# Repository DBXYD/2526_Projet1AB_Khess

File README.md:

# 🎓 2526_Projet1AB_Khess
> [!Note]
> Projet de 1ère année ENSEA sur une caisse enregistreuse pour la K-Fet.

> [!Important]
> Ce projet reprend en partie le travail de Matis Garbez, disponible sur [2425_Maker_CashRegister](https://github.com/Volcanite/2425_Maker_CashRegister/).

## 📋 Sommaire
- [Cahier des charges](#cahier-des-charges)
	- [Caisse enregistreuse portable avec écran tactile](#caisse-enregistreuse-portable-avec-%C3%A9cran-tactile)
	- [Contraintes](#contraintes)
- [Hardware](#hardware)
- [Modèle 3D de la caisse](#mod%C3%A8le-3d-de-la-caisse)
- [Partie Logicielle (Software)](#partie-logicielle-software)
	- [Accès au Code Source et Déploiement](#acc%C3%A8s-au-code-source-et-d%C3%A9ploiement)
	- [Architecture de la Base de Données](#architecture-de-la-base-de-donn%C3%A9es)
- [Technologies utilisées](#technologies-utilis%C3%A9es)
- [Avancée du projet](#avanc%C3%A9e-du-projet)
	- [Journal de bord](#journal-de-bord)
	- [Ce qui a été réalisé](#ce-qui-a-%C3%A9t%C3%A9-r%C3%A9alis%C3%A9)
	- [Ce qui n'a pas (encore) été réalisé](#ce-qui-na-pas-encore-ete-r%C3%A9alis%C3%A9)
	- [Problèmes rencontrés et solutions trouvées](#probl%C3%A8mes-rencontr%C3%A9s-et-solutions-trouv%C3%A9es)
	- [Améliorations possibles](#am%C3%A9liorations-possibles)
- [Membres du projet](#membres-du-projet)
- [Licence](#licence)

## 📝 Cahier des charges 

### 📱 Caisse enregistreuse portable avec écran tactile 
* Interface utilisateur intuitive
* Gestion des produits et des prix
* Paiement avec carte étudiante

### ⚠️ Contraintes 
* Portabilité (batterie) : terminal de paiement
* Fiabilité des transactions
* Sécurité des données

## 🔧 Hardware 
Voir [Hardware/README.md](Hardware/README.md).

## 🖨️ Modèle 3D de la caisse 
La caisse automatique est consituée de 3 éléments :
- la caisse entière avec le socle
- le module de paiement
- le support pour la tablette
  
La modélisation 3D de ces différentes pièces à été réaliser avec le logiciel Onshape, voici les liens correspondant : 
* [Caisse entière avec socle](3D/Caisse%20entière%20avec%20socle.stl) 
* [Module paiement final](3D/Module%20payement%20final.stl)
* [Support tablette final](3D/Support%20tablette%20final.stl)

## 💻 Partie Logicielle (Software) 
Cette section regroupe l'ensemble du code source de l'application web de la caisse connectée, développée avec le framework **Django** (Python).

### 🔗 Accès au Code Source et Déploiement 

> **Note sur le dépôt :** Suite à des difficultés techniques lors de la synchronisation et de l'envoi du code sur le dépôt partagé de l'équipe, la version la plus récente et totalement à jour de l'application a été temporairement hébergée sur mon espace personnel.

* **Code source à jour :** Vous pouvez consulter et récupérer l'intégralité du projet en [cliquant directement sur ce lien vers mon dépôt personnel](https://github.com/zhang-estelle/DatabaseCashRegister).
* **Guide d'installation :** Pour faire fonctionner le code facilement sur votre machine, j'ai rédigé un guide pas-à-pas. Ce tutoriel recense également l'ensemble des blocages et des problèmes techniques que j'ai rencontrés durant le développement ainsi que leurs solutions. [Consulter le tutoriel de configuration Django](Docs/TutoDjango.md).

### 🗄️ Architecture de la Base de Données 

Le système s'appuie sur une base de données relationnelle structurée pour gérer les profils des étudiants, leurs soldes (cotisants ou non), le catalogue de la K-FET et l'historique des ventes.

* **Modèle Conceptuel :** Pour comprendre l'organisation de nos tables, vous pouvez [accéder au schéma graphique dbdiagram](Docs/dbdiagram.pdf).

## ⚙️ Technologies utilisées 
- Python
- Django
- Raspberry Pi
- KiCad
- Onshape
- Impression 3D

## ✅ Avancée du projet 

### 📓 Journal de bord 
Voir [Journal_de_bord.md](Docs/Journal_de_bord.md).

### ✅ Ce qui a été réalisé 
* Prise en main du projet
* Création des PCB
* Soudure des PCB
* Développement du site internet/ interface vendeur avec gestion des stocks, des commandes
* Modification 3D de la caisse en changeant les dimensions du socle soutenant la tablette
* Modélisation 3D du module de paiement avec plusieurs variantes afin de correspondre à la taille du PCB contenu à l'intérieur
* Développement du code du module de payement
* Modification 3D de la caisse en changeant le support tablette se mettant sur le socle
* Test du PCB

### ❌ Ce qui n'a pas (encore) été réalisé 
* Assemblage de l'ensemble

### 🛠️ Problèmes rencontrés et solutions trouvées 
Modélisation 3D:
- La taille du support de tablette était trop petite ( impossibilité de passer les câbles HDMI et USB vers la caisse automatique ). 
On a du imprimer plusieurs fois le support pour trouver la taille adéquate.
- Les trous pour fixer le support de tablette à son support n'étaient pas au bonne endroit après l'impression, on a du percer avec une perceuse les trous pour fixer le support correctement. 
- Problèmes usuels d'impression 3D.

### 💡 Améliorations possibles 
* Revoir le design de la caisse
* Améliorer le site internet

## 👥 Membres du projet 
|  |  |  |  |  |  |  |
| :---: | :---: | :---: | :---: | :---: | :---: | :---: |
| [@Ahhj93](https://github.com/Ahhj93)<br>Bryan-Sowanna Ing | [@NKRIMAT](https://github.com/NKRIMAT)<br>Naïm Krimat | [@Margaux-Lapl](https://github.com/Margaux-Lapl)<br>Margaux Laplante | [@StrangeKobe](https://github.com/StrangeKobe)<br>Rayan Laghouane | [@zhang-estelle](https://github.com/zhang-estelle)<br>Estelle Zhang | [@ClementJ493](https://github.com/ClementJ493)<br>Clément Jouneau | [@rim-05-mma](https://github.com/rim-05-mma)<br>Rim Bouchikhi |

## 📄 Licence 
Ce projet est distribué sous la licence MIT — voir [LICENSE](LICENSE).

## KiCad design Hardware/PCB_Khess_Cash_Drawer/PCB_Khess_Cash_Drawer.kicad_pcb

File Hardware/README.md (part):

# 🔧 Hardware

## 📋 Sommaire
- [Schéma d'architecture](#schema-architecture)
- [PCB_Khess_Cash_Drawer](#pcb_khess_cash_drawer)
    - [Schéma](#sch%C3%A9ma)
    - [Liste des composants du PCB](#liste-des-composants-du-pcb)
    - [Liste des composants autres](#liste-des-composants-autres)
    - [Justification des choix techniques](#justification-des-choix-techniques)
        - [Architecture d’alimentation](#architecture-dalimentation)
        - [Protections électriques](#protections-%C3%A9lectriques)
        - [Commande du tiroir caisse](#commande-du-tiroir-caisse)
    - [Ouverture du tiroir caisse (Raspberry Pi 4)](#ouverture-du-tiroir-caisse-raspberry-pi-4)
    - [PCB](#pcb)
- [PCB_Khess_Module_Payment](#pcb_khess_module_payment)
    - [Schéma](#sch%C3%A9ma-1)
    - [Liste des composants du PCB](#liste-des-composants-du-pcb-1)
    - [Liste des composants autres](#liste-des-composants-autres-1)
    - [Justification des choix techniques](#justification-des-choix-techniques-1)
        - [Raspberry Pi Zero 2W](#raspberry-pi-zero-2w)
        - [Interface RFID](#interface-rfid)
        - [Interface écran](#interface-%C3%A9cran)
        - [Clavier numérique](#clavier-num%C3%A9rique)
    - [PCB](#pcb-1)

## 🔎 Schéma d'architecture 

Voici une représentation Mermaid du schéma :

```mermaid
flowchart LR
    subgraph Caisse_principale[ Caisse principale ]
        A230(230V AC) --> A12(12V DC)
        A12 --> A5(5V DC)
        A5 --> RPi4[Raspberry Pi 4]
        A12 --> CmdT[Commande tiroir]
        CmdT --> Tiroir[Tiroir caisse]
        RPi4 -->|HDMI| Ecran[Ecran]
        RPi4 -->|GPIO| CmdT
        RPi4 -->|WiFi| Serveur[Serveur]
    end

    subgraph Module_paiement[ Module de paiement ]
        Shield[Shield + gestion batterie] --> RPi0[Raspberry Pi Zero 2W]
        RPi0 -->|HDMI| Ecran2[Ecran]
        RPi0 -->|SPI| RFID[Capteur RFID]
        RPi0 --> Clavier[Clavier]
    end

    RPi4 -->|Bluetooth| RPi0
```

## 🧾 PCB_Khess_Cash_Drawer 
### 🗺️ Schéma 
<details>
<summary>Afficher le schéma</summary>

</details>

### 🔩 Liste des composants du PCB 

* Convertisseur 12V à 5V DC
    * 1 Convertisseur R-78B5.0-2.0 ([datasheet](/Datasheets/PCB_Khess_Cash_Drawer/R-78B-2.0.pdf))
    * 1 Condensateur 10uF
    * 1 Condensateur 4,7uF
    * 1 Bobine 10uH

* Conventisseur 230V à 12V DC
    * 1 Porte-fusible
    * 1 Convertisseur PSK-15E-12 ([datasheet](/Datasheets/PCB_Khess_Cash_Drawer/psk-15e.pdf))
    * 1 Condensateur 100uF
    * 1 Condensateur 1uF
    * 1 Diode TVS (824 500 500) ([datasheet](/Datasheets/PCB_Khess_Cash_Drawer/824500500.pdf))
    * 1 Résistance bobinée 6,8 Ohm (remplacée par un fil) ([datasheet](/Datasheets/PCB_Khess_Cash_Drawer/ac_ac-at_ac-ni.pdf))
    * 1 Varistance TVS 10D561K (non mise) ([datasheet](/Datasheets/PCB_Khess_Cash_Drawer/mov10d.pdf))

* Commande du tiroir caisse
    * 1 Diode DST10100S ([datasheet](/Datasheets/PCB_Khess_Cash_Drawer/littelfuse-rectifier-DST10100S-datasheet.pdf))
    * 1 Transistor BUK9637-100E,118 ([datasheet](/Datasheets/PCB_Khess_Cash_Drawer/BUK9637-100E.pdf))
    * 1 Résistance 220 Ohm
    * 1 Résistance 10k Ohm

* Connecteurs
    * 1 Connecteur 01x03
    * 1 Connecteur RJ11, remplacée par 1 Connecteur 01x02
    * 1 Bornier à vis 01x02
    * 1 Écran tactile

### 📦 Liste des composants autres 

* Tiroir caisse avec connecteur standard RJ11, remplacée par des connecteurs simples
* Câble d'alimentation
* Raspberry Pi 4

## ⚙️ Justification des choix techniques 

### 🔌 Architecture d’alimentation 

L’alimentation du système est réalisée en deux étapes afin d’assurer une conversion efficace et stable :

1. Conversion du secteur 230V AC vers 12V DC ;
2. Conversion du 12V DC vers 5V DC.

Le module **PSK-15E-12** a été choisi car il permet :
- une intégration compacte directement sur le PCB ;
- une puissance suffisante pour alimenter le tiroir caisse et les circuits logiques.

Le convertisseur **R-78B5.0-2.0** a été préféré à un régulateur linéaire classique pour son excellent rendement énergétique. Cela permet - d’éviter l’ajout d’un dissipateur thermique ;
- d’assurer une alimentation stable du Raspberry Pi.

Les condensateurs et la bobine de filtrage permettent de réduire les parasites haute fréquence et d’améliorer la stabilité des tensions d’alimentation.

### 🛡️ Protections électriques 

Plusieurs composants de protection ont été ajoutés afin d’améliorer la robustesse du système :

- le porte-fusible protège la carte en cas de court-circuit ;
- la diode TVS protège contre les surtensions transitoires ;
- la varistance devait initialement renforcer la protection contre les pics secteur ;
- les condensateurs participent au filtrage des perturbations électromagnétiques.

Ces protections sont importantes car le système est directement relié au secteur et pilote une charge inductive.

### ⚡ Commande du tiroir caisse 

Le tiroir caisse est commandé via un MOSFET de puissance **BUK9637-100E**. Ce composant a été choisi pour :
- sa faible résistance à l’état passant ;
- sa capacité à commuter des courants importants ;
- sa compatibilité avec les niveaux logiques du Raspberry Pi.

La diode **DST10100S** agit comme diode de roue libre afin d’absorber les surtensions générées lors de la coupure du courant dans l’électroaimant du tiroir caisse.

La résistance de 220 Ω limite le courant de commande du MOSFET tandis que la résistance de 10 kΩ garantit son extinction au démarrage.

### 🚪 Ouverture du tiroir caisse (Raspberry Pi 4) 

L’ouverture du tiroir caisse se fait via le PCB :

1. La **Raspberry Pi 4** envoie un signal de commande sur un **GPIO** ;
2. Le GPIO pilote la grille du **MOSFET** sur le PCB ;
3. Le MOSFET commute l’alimentation **12V** de l’électroaimant du tiroir ;
4. Le tiroir caisse s’ouvre pendant l’impulsion.

Nous n’avions pas de port **RJ11** disponible sur notre montage.  
Nous avons donc remplacé les connecteurs RJ11 par des **pinheaders**.

### 🧩 PCB 
<details>
<summary>Voir PCB (face côté avant)</summary>

</details>

<details>
<summary>Voir PCB (face arrière)</summary>

</details>

---

## 🧾 PCB_Khess_Module_Payment 
### 🗺️ Schéma 
<details>
<summary>Afficher le schéma</summary>

</details>

### 🔩 Liste des composants du PCB 

* Raspberry Pi
    * 1 Connecteur 02x20
    * 1 Diode TVS (824 500 500) ([datasheet](/Datasheets/PCB_Khess_Cash_Drawer/824500500.pdf))
    * 2 Résistances 470 Ohm
    * 2 LED
    * 1 Condensateur 100nF

* RFID
    * 1 Connecteur 01x08
    * 1 Condensateur 1uF

* Écran
    * 1 Condensateur 1uF
    * 1 Connecteur 01x04
    * 2 Résistances 4,7k Ohm

* Clavier numérique
    * 4 Résistances 10k Ohm
    * 4 Résistances 330 Ohm
    * 1 Connecteurs 01x08

### 📦 Liste des composants autres 

* 1 Raspberry Zero 2W
* 1 Écran tactile
* 1 Clavier numérique
* 1 Capteur RFID
* 1 Shield pour gérer une batterie

### ⚙️ Justification des choix techniques 

#### 🖥️ Raspberry Pi Zero 2W 

Le Raspberry Pi Zero 2W a été choisi comme unité centrale du module de paiement pour plusieurs raisons :
- faible consommation énergétique ;
- connectivité Wi-Fi intégrée ;
- puissance suffisante pour gérer l’interface utilisateur et les périphériques.

#### 🛰️ Interface RFID 

Le module RFID permet l’identification sans contact des utilisateurs.

Le connecteur 01x08 qui permet la comminication via le bus SPI, facilite le remplacement ou la maintenance du module RFID. Le condensateur de 1 µF améliore la stabilité de son alimentation et limite les perturbations lors des communications.

#### 🖱️ Interface écran 

L’écran tactile est connecté via une interface dédiée afin de simplifier le montage.

Les résistances de pull-up de 4,7 kΩ servent de résistances de tirage pour les lignes de communication utilisées en I2C.

Le condensateur de 1 µF stabilise l’alimentation de l’écran et réduit les parasites.

#### 🔢 Clavier numérique 

Le clavier numérique permet une interaction simple avec l’utilisateur et sert dans le cas où l'utilisateur ne possède pas sa carte.

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
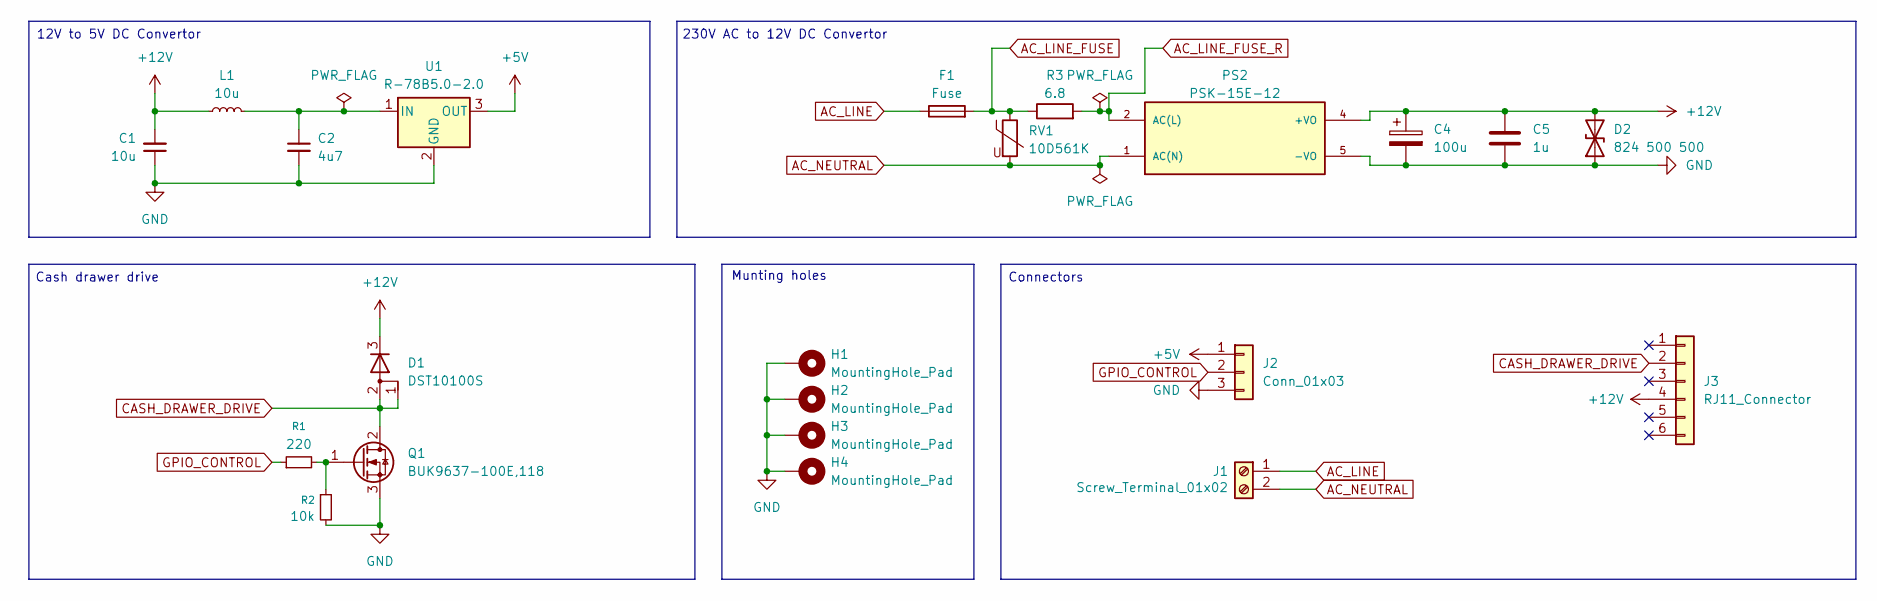
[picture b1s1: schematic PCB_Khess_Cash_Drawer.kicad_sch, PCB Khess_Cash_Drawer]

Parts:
C1: 10u; C_0805_2012Metric
C2: 4u7; C_0805_2012Metric
C4: 100u; CP_Elec_6.3x7.7
C5: 1u; C_0805_2012Metric
D1: DST10100S; TO-277A
D2: 824 500 500; D_SMA
F1: Fuse; Fuseholder_Cylinder-5x20mm_Schurter_0031_8201_Horizontal_Op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
H1, H2, H3, H4: MountingHole_Pad; MountingHole_2.7mm_M2.5_Pad
J1: Screw_Terminal_01x02; TerminalBlock_Phoenix_PT-1,5-2-5.0-H_1x02_P5.00mm_Horizontal
J2: Conn_01x03; PinHeader_1x03_P2.54mm_Vertical
J3: RJ11_Connector; RJ12_Amphenol_54601-x06_Horizontal
L1: 10u; L_0805_2012Metric
PS2: PSK-15E-12; CONV_PSK-15E-12; PARTREV 1.0
Q1: BUK9637-100E,118; TO-263-2
R1: 220; R_0603_1608Metric
R2: 10k; R_0603_1608Metric
R3: 6.8; R_Axial_DIN0414_L11.9mm_D4.5mm_P20.32mm_Horizontal
RV1: 10D561K; VAR_MOV-10D561K
U1: R-78B5.0-2.0; Converter_DCDC_RECOM_R-78B-2.0_THT

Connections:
+5V: J2.1, U1.3 (OUT)
+12V: C1.2, C4.1, C5.1, D1.3 (K), D2.2 (A2), J3.4, L1.1, PS2.4 (+VO)
AC_LINE: F1.1, J1.1
AC_LINE_FUSE: F1.2, R3.1, RV1.1
AC_LINE_FUSE_R: PS2.2 (AC(L)), R3.2
AC_NEUTRAL: J1.2, PS2.1 (AC(N)), RV1.2
CASH_DRAWER_DRIVE: D1.1 (A), D1.2 (A), J3.2, Q1.2 (D)
GND: C1.1, C2.2, C4.2, C5.2, D2.1 (A1), H1.1, H2.1, H3.1, H4.1, J2.3, PS2.5 (-VO), Q1.3 (S), R2.2, U1.2 (GND)
GPIO_CONTROL: J2.2, R1.1
unnamed: Q1.1 (G), R1.2, R2.1
unnamed: C2.1, L1.2, U1.1 (IN)

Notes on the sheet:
Connectors
230V AC to 12V DC Convertor
Munting holes
Cash drawer drive
12V to 5V DC Convertor

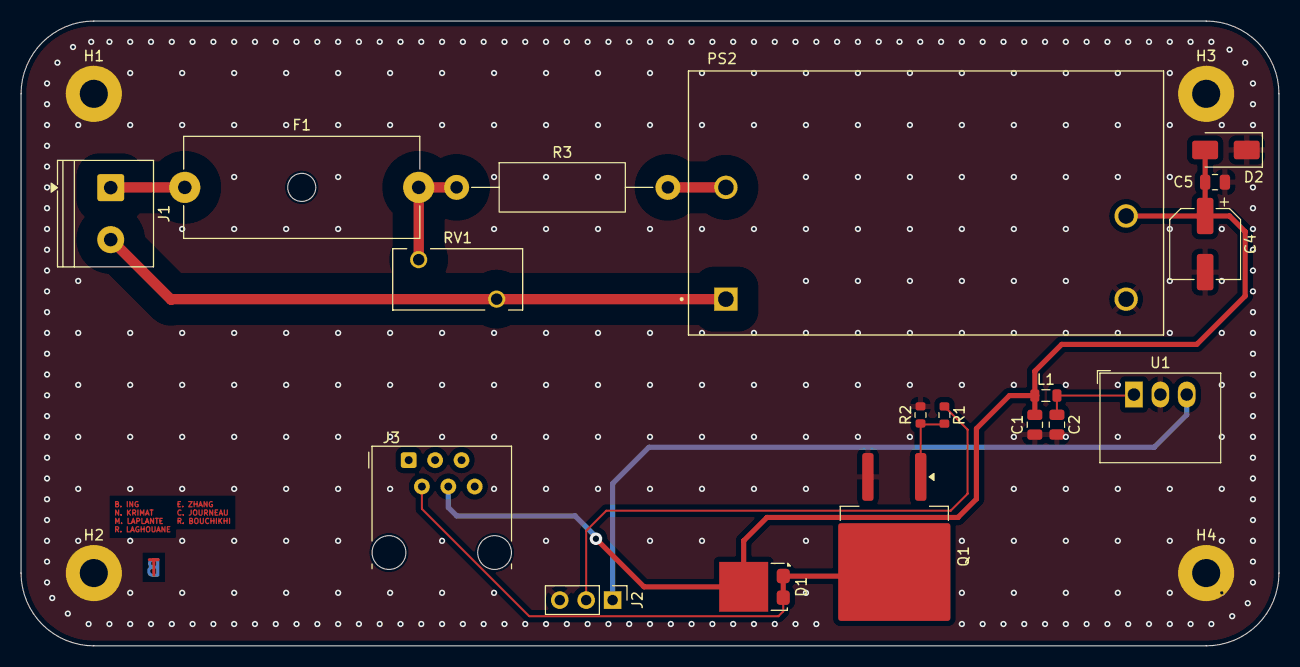
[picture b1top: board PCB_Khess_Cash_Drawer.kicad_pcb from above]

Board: 2 copper layers, 121.0 x 60.1 mm, 22 parts (0 on the bottom side), 11 nets.

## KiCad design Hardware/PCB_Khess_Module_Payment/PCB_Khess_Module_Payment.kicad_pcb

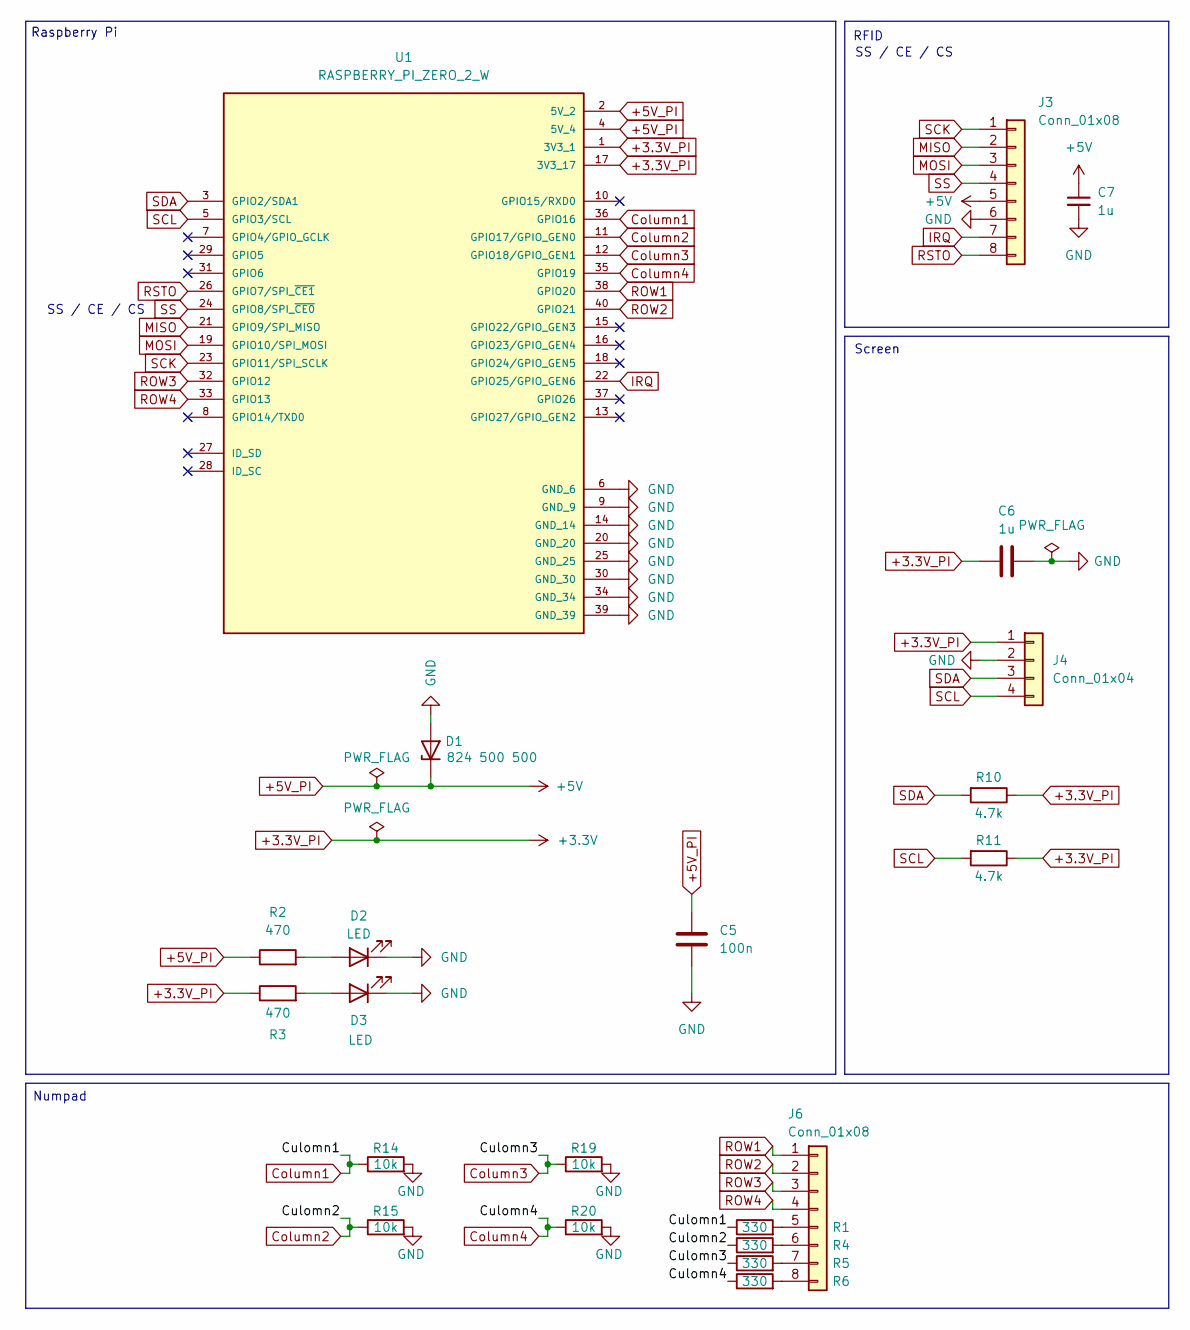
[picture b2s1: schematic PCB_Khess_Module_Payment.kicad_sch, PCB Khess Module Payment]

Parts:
C5: 100n; C_0402_1005Metric
C6, C7: 1u; C_0603_1608Metric
D1: 824 500 500; D_SMA
D2, D3: LED; LED_0603_1608Metric
J3, J6: Conn_01x08; PinHeader_1x08_P2.54mm_Horizontal
J4: Conn_01x04; PinHeader_1x04_P2.54mm_Horizontal
R1, R4, R5, R6: 330; R_0402_1005Metric
R2, R3: 470; R_0805_2012Metric
R10, R11: 4.7k; R_0402_1005Metric
R14, R15, R19, R20: 10k; R_0805_2012Metric
U1: RASPBERRY_PI_ZERO_2_W; MODULE_RASPBERRY_PI_ZERO_2_W; PARTREV April 2024

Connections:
+3.3V_PI: C6.1, J4.1, R3.1, R10.1, R11.1, U1.1 (3V3_1), U1.17 (3V3_17)
+5V_PI: C5.1, C7.1, D1.1 (K), J3.5, R2.1, U1.2 (5V_2), U1.4 (5V_4)
Column1: R1.1, R14.1, U1.36 (GPIO16)
Column2: R4.1, R15.1, U1.11 (GPIO17/GPIO_GEN0)
Column3: R5.1, R19.1, U1.12 (GPIO18/GPIO_GEN1)
Column4: R6.1, R20.1, U1.35 (GPIO19)
GND: C5.2, C6.2, C7.2, D1.2 (A), D2.1 (K), D3.1 (K), J3.6, J4.2, R14.2, R15.2, R19.2, R20.2, U1.6 (GND_6), U1.9 (GND_9), U1.14 (GND_14), U1.20 (GND_20), U1.25 (GND_25), U1.30 (GND_30), U1.34 (GND_34), U1.39 (GND_39)
IRQ: J3.7, U1.22 (GPIO25/GPIO_GEN6)
MISO: J3.2, U1.21 (GPIO9/SPI_MISO)
MOSI: J3.3, U1.19 (GPIO10/SPI_MOSI)
unnamed: D2.2 (A), R2.2
unnamed: D3.2 (A), R3.2
unnamed: J6.5, R1.2
unnamed: J6.6, R4.2
unnamed: J6.7, R5.2
unnamed: J6.8, R6.2
ROW1: J6.1, U1.38 (GPIO20)
ROW2: J6.2, U1.40 (GPIO21)
ROW3: J6.3, U1.32 (GPIO12)
ROW4: J6.4, U1.33 (GPIO13)
RSTO: J3.8, U1.26 (GPIO7/SPI_~CE1)
SCK: J3.1, U1.23 (GPIO11/SPI_SCLK)
SCL: J4.4, R11.2, U1.5 (GPIO3/SCL)
SDA: J4.3, R10.2, U1.3 (GPIO2/SDA1)
SS: J3.4, U1.24 (GPIO8/SPI_~CE0)

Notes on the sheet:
RFID
Raspberry Pi
Numpad
Screen
SS / CE / CS

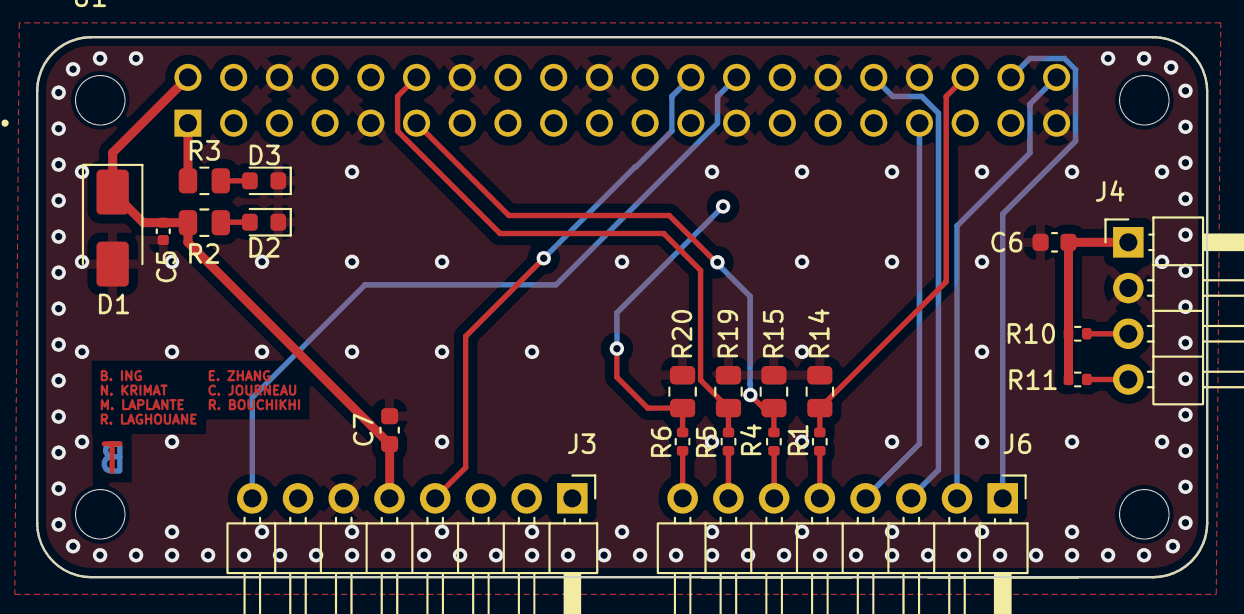
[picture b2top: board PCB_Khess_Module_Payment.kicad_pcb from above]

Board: 4 copper layers, 65.0 x 30.0 mm, 22 parts (0 on the bottom side), 25 nets.

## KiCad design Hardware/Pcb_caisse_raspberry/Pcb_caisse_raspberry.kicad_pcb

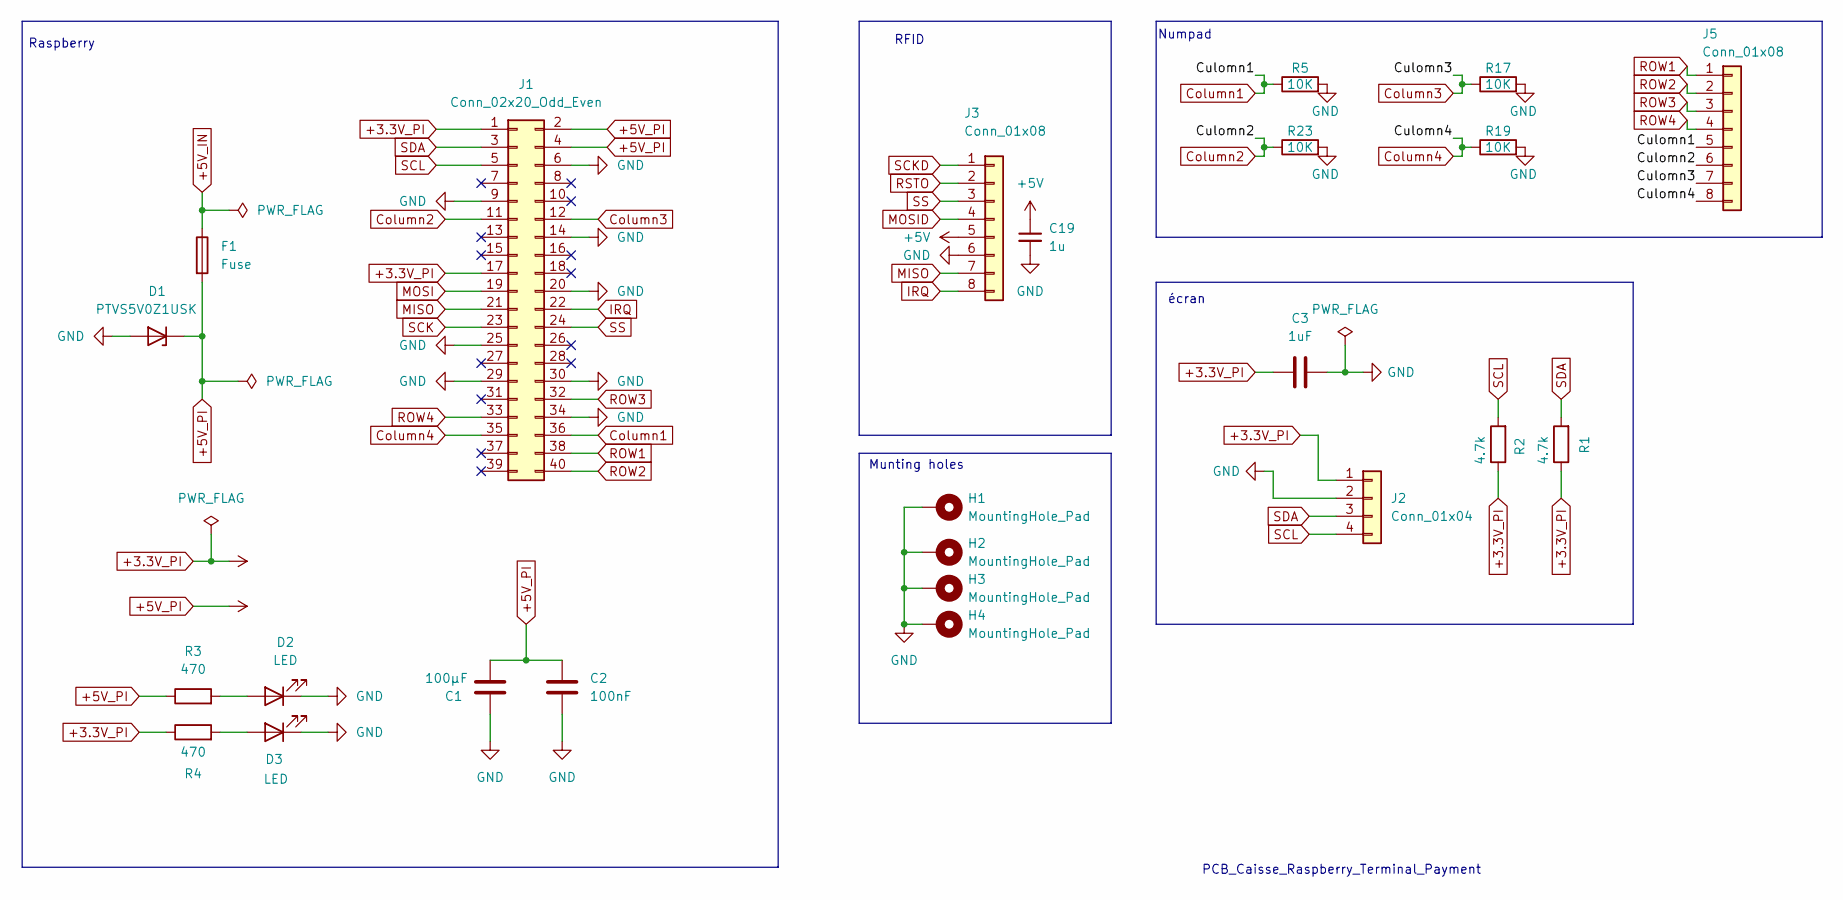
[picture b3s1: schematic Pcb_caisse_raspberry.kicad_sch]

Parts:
C1: 100µF; C_0603_1608Metric_Pad1.08x0.95mm_HandSolder
C2: 100nF; C_0603_1608Metric_Pad1.08x0.95mm_HandSolder
C3: 1uF; C_0603_1608Metric_Pad1.08x0.95mm_HandSolder
C19: 1u; C_0603_1608Metric_Pad1.08x0.95mm_HandSolder
D1: PTVS5V0Z1USK; Nexperia_DSN1608-2_1.6x0.8mm
D2, D3: LED; LED_0603_1608Metric_Pad1.05x0.95mm_HandSolder
F1: Fuse; FuseHolder_Blade_ATO_Littelfuse_FLR_178.6165
H1, H2, H3, H4: MountingHole_Pad; MountingHole_2.7mm_M2.5_Pad
J1: Conn_02x20_Odd_Even; PinHeader_2x20_P1.00mm_Vertical
J2: Conn_01x04; PinHeader_1x04_P2.54mm_Horizontal
J3, J5: Conn_01x08; PinHeader_1x08_P2.54mm_Horizontal
R1, R2: 4.7k; R_0603_1608Metric_Pad0.98x0.95mm_HandSolder
R3, R4: 470; R_0603_1608Metric_Pad0.98x0.95mm_HandSolder
R5, R17, R19, R23: 10K; R_0402_1005Metric

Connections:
+3.3V_PI: C3.1, J1.1, J1.17, J2.1, R1.1, R2.1, R4.1
+5V_IN: F1.1
+5V_PI: C1.2, C2.1, C19.1, D1.1 (K), F1.2, J1.2, J1.4, J3.5, R3.1
Column1: J1.36, J5.5, R5.1
Column2: J1.11, J5.6, R23.1
Column3: J1.12, J5.7, R17.1
Column4: J1.35, J5.8, R19.1
GND: C1.1, C2.2, C3.2, C19.2, D1.2 (A), D2.1 (K), D3.1 (K), H1.1, H2.1, H3.1, H4.1, J1.6, J1.9, J1.14, J1.20, J1.25, J1.29, J1.30, J1.34, J2.2, J3.6, R5.2, R17.2, R19.2, R23.2
IRQ: J1.22, J3.8
MISO: J1.21, J3.7
MOSI: J1.19
MOSID: J3.4
unnamed: D2.2 (A), R3.2
unnamed: D3.2 (A), R4.2
ROW1: J1.38, J5.1
ROW2: J1.40, J5.2
ROW3: J1.32, J5.3
ROW4: J1.33, J5.4
RSTO: J3.2
SCK: J1.23
SCKD: J3.1
SCL: J1.5, J2.4, R2.2
SDA: J1.3, J2.3, R1.2
SS: J1.24, J3.3

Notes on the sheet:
Munting holes
RFID
Raspberry
Numpad
écran
PCB_Caisse_Raspberry_Terminal_Payment

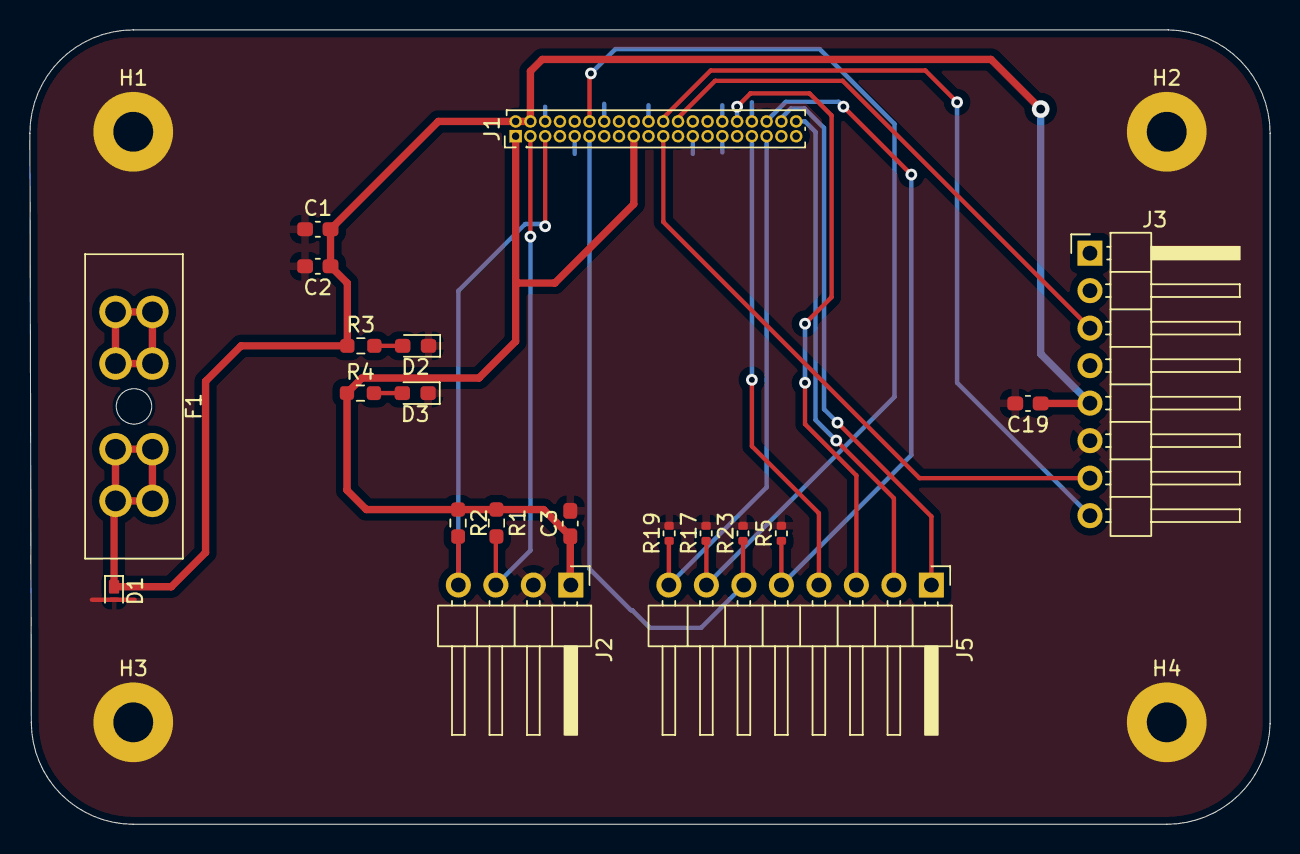
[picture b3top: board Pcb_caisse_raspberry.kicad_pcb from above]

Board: 2 copper layers, 84.0 x 53.8 mm, 24 parts (0 on the bottom side), 18 nets.

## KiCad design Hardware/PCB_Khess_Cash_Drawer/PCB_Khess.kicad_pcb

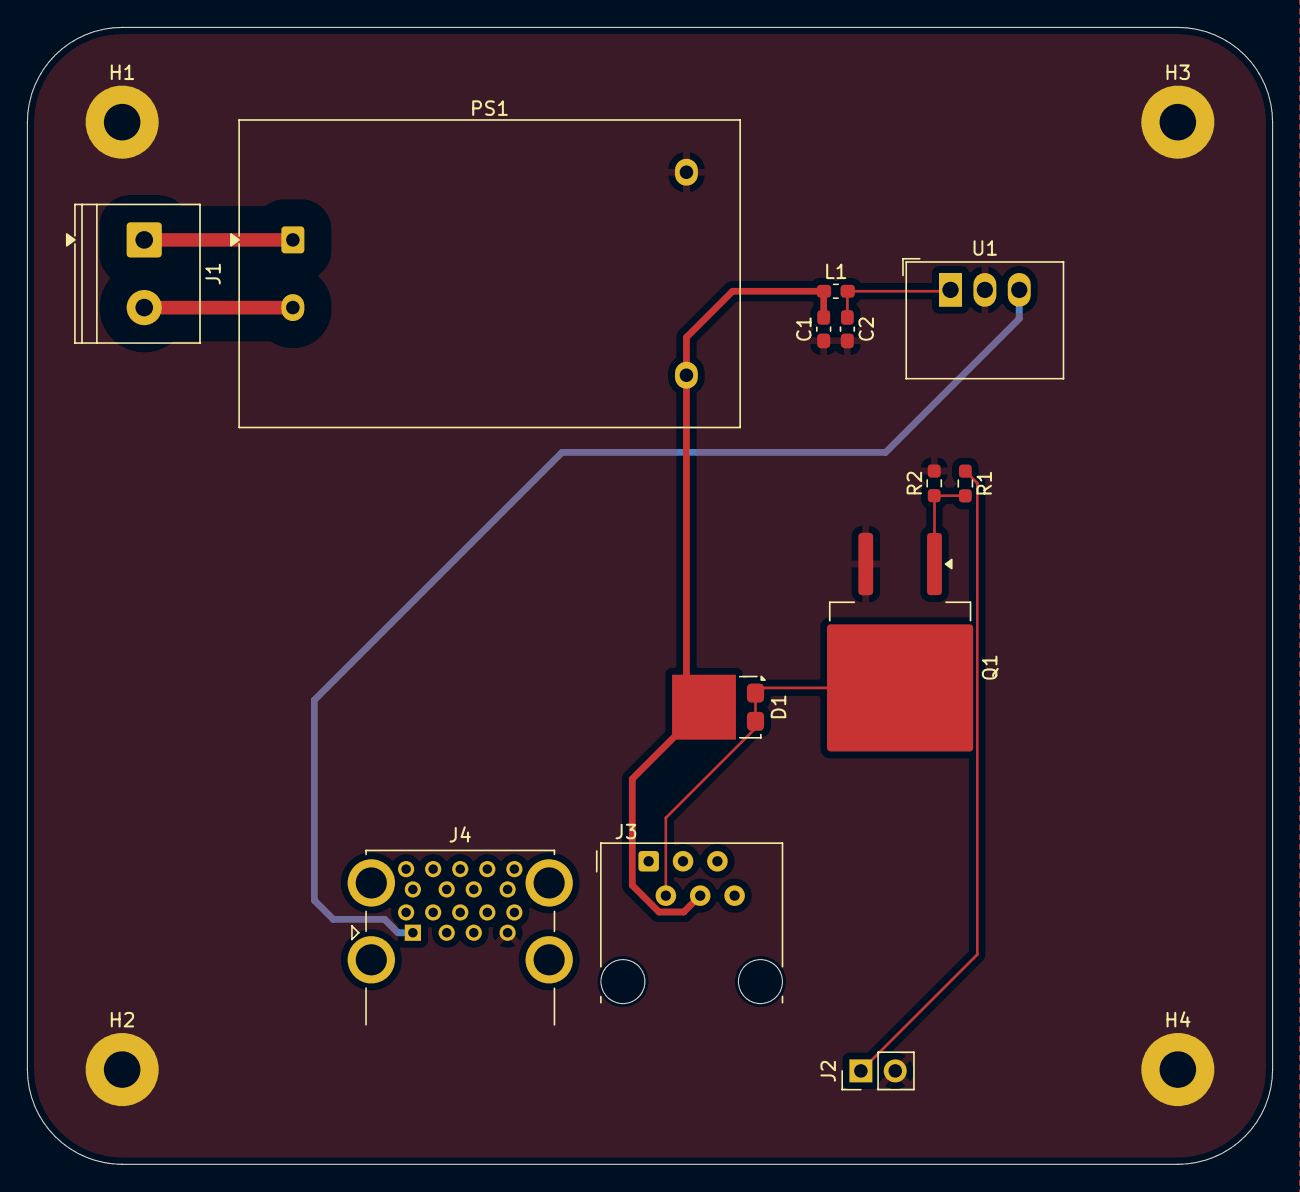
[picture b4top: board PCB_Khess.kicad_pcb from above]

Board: 2 copper layers, 92.0 x 84.0 mm, 17 parts (0 on the bottom side), 9 nets.

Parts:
C1: 10u; C_0603_1608Metric_Pad1.08x0.95mm_HandSolder
C2: 4.7u; C_0603_1608Metric_Pad1.08x0.95mm_HandSolder
D1: DST10100S; TO-277A
H1, H2, H3, H4: MountingHole_Pad; MountingHole_2.7mm_M2.5_Pad
J1: Screw_Terminal_01x02; TerminalBlock_Phoenix_PT-1,5-2-5.0-H_1x02_P5.00mm_Horizontal
J2: Conn_01x02; PinHeader_1x02_P2.54mm_Vertical
J3: RJ11_Connector; RJ12_Amphenol_54601-x06_Horizontal
J4: USB3_A; USB3_A_Molex_48406-0001_Horizontal_Stacked
L1: 10u; L_0603_1608Metric_Pad1.05x0.95mm_HandSolder
PS1: HLK-PM12; Converter_ACDC_Hi-Link_HLK-PMxx
Q1: BUK9637-100E,118; TO-263-2
R1: 220; R_0603_1608Metric_Pad0.98x0.95mm_HandSolder
R2: 10k; R_0603_1608Metric_Pad0.98x0.95mm_HandSolder
U1: R-78B5.0-2.0; Converter_DCDC_RECOM_R-78B-2.0_THT

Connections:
+5V: J4.1 (VBUS), U1.3 (OUT)
AC_LINE: J1.1, PS1.1 (AC/L)
AC_NEUTRAL: J1.2, PS1.2 (AC/N)
CASH_DRAWER_DRIVE: D1.1 (A), D1.2 (A), J3.2, Q1.2 (D)
CASH_DRAWER_VCC: C1.2, D1.3 (K), J3.4, L1.1, PS1.4 (+Vout)
GND: C1.1, C2.2, H1.1, H2.1, H3.1, H4.1, J2.2, J4.4 (GND), PS1.3 (-Vout), Q1.3 (S), R2.2, U1.2 (GND)
GPIO_CONTROL: J2.1, R1.1
unnamed: Q1.1 (G), R1.2, R2.1
unnamed: C2.1, L1.2, U1.1 (IN)

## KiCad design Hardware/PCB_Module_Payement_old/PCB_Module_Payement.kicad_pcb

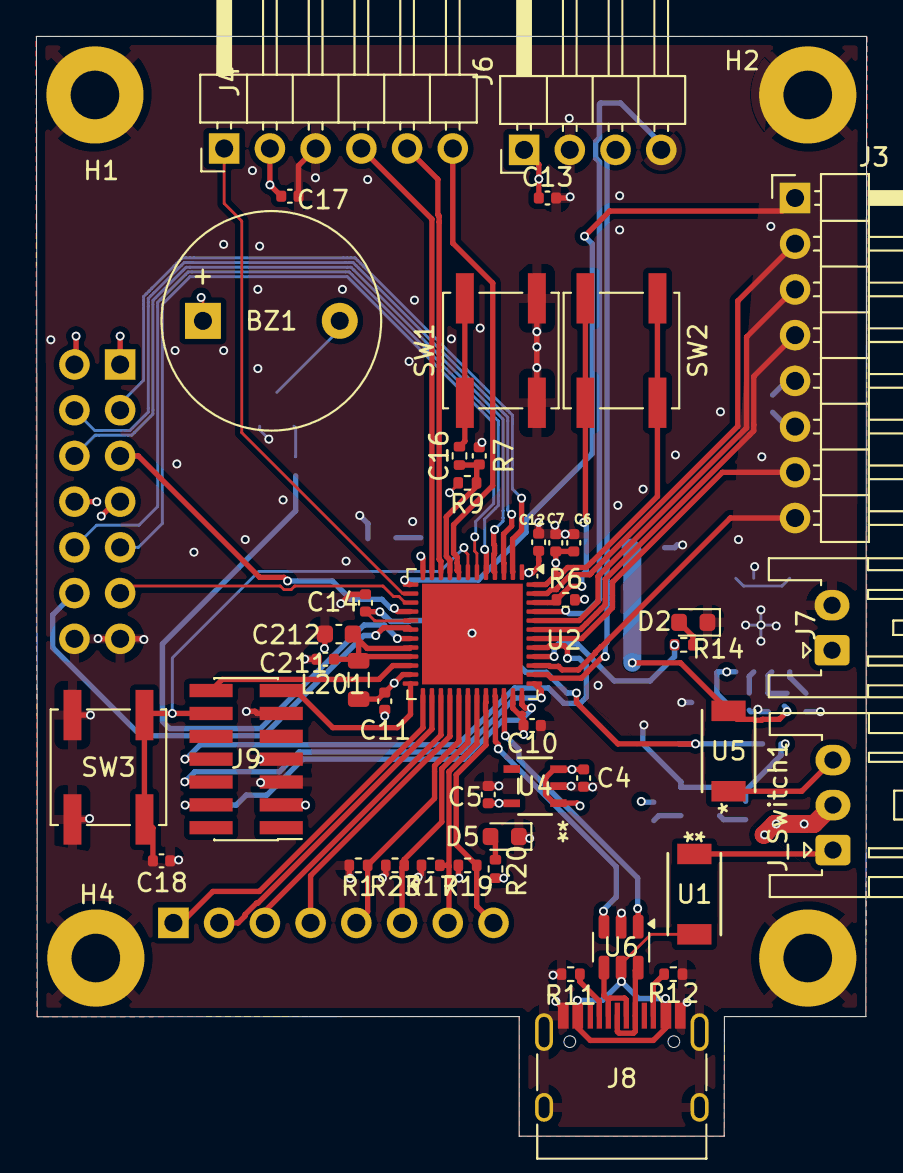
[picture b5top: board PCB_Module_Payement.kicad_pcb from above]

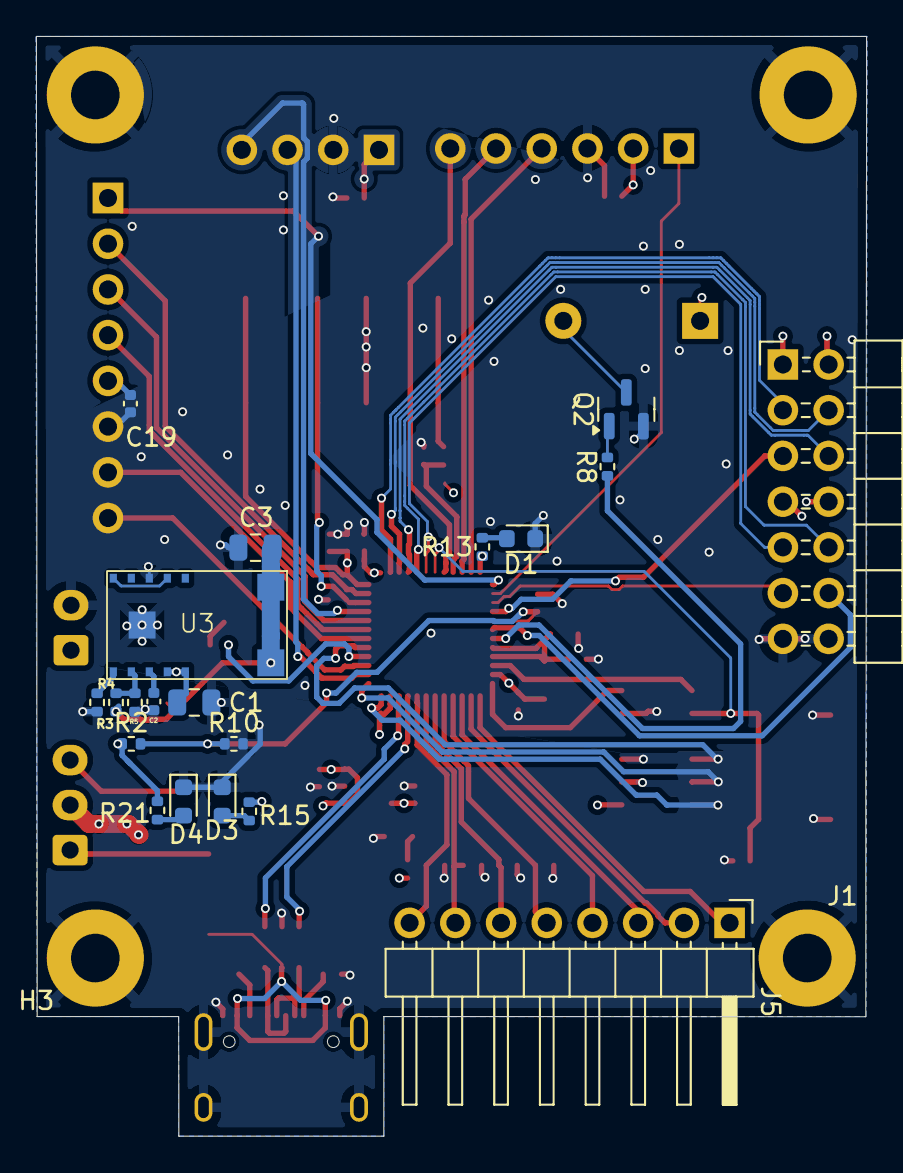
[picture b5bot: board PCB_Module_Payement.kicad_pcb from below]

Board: 4 copper layers, 46.1 x 61.1 mm, 68 parts (20 on the bottom side), 67 nets.

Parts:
BZ1: Buzzer; Buzzer_12x9.5RM7.6
C1: 10u; C_0805_2012Metric
C2, C4, C5, C13, C17, C19: 1u; C_0402_1005Metric
C3: 47u; C_0805_2012Metric
C6: 4u7; C_0402_1005Metric
C7, C10, C11, C12, C14, C16, C18, C211: 100n; C_0402_1005Metric
C212: 1u; C_0603_1608Metric
D1: LED Blue; LED_0603_1608Metric
D2: LED Amber; LED_0603_1608Metric
D3: LED Yellow; LED_0603_1608Metric
D4: LED_Blue; LED_0603_1608Metric
D5: LED_Green; LED_0603_1608Metric
H1, H2, H3, H4: MountingHole_Pad; MountingHole_2.7mm_M2.5_Pad
J1: Conn_02x07_Odd_Even; PinHeader_2x07_P2.54mm_Horizontal
J3, J5: Conn_01x08; PinHeader_1x08_P2.54mm_Horizontal
J4: Conn_01x06; PinHeader_1x06_P2.54mm_Horizontal
J6: Conn_01x04; PinHeader_1x04_P2.54mm_Horizontal
J7: Conn_01x02; JST_XA_S02B-XASK-1_1x02_P2.50mm_Horizontal
J8: USB_C_Receptacle_USB2.0; USB_C_Receptacle_HRO_TYPE-C-31-M-12
J9: Conn_ST_STDC14; PinHeader_2x07_P1.27mm_Vertical_SMD
J_Switch1: Conn_01x03; JST_XA_S03B-XASK-1_1x03_P2.50mm_Horizontal
L201: 39n; L_0805_2012Metric
Q2: MMBT2222A; SOT-23
R1, R17, R19, R23: 10K; R_0402_1005Metric
R2: 168K; R_0402_1005Metric
R3: 5k6; R_0402_1005Metric
R4: 49k9; R_0402_1005Metric
R5, R6, R7, R9: 10k; R_0402_1005Metric
R8: 1K; R_0402_1005Metric
R10: 68K; R_0402_1005Metric
R11, R12: 5.1K; R_0402_1005Metric
R13, R14, R15: 1k7; R_0402_1005Metric
R20: 510; R_0402_1005Metric
R21: R; R_0402_1005Metric
SW1, SW2, SW3: SW_Push; SW_Push_1P1T_NO_CK_KSC6xxJ
U1, U5: FSV330AF; DO-214AD_ONS
U2: STM32G431CBUx; QFN-48-1EP_7x7mm_P0.5mm_EP5.6x5.6mm
U3: 171013801; Wurth_171013801
U4: BU33SD5WG-TR; SSOP5_ROM
U6: USBLC6-2SC6; SOT-23-6

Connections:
5V_BUCK: C3.1, R4.1, U3.6 (Vout), U3.7 (Vout), U5.2 (A)
5V_USB: J8.A4 (VBUS), J8.A9 (VBUS), J8.B4 (VBUS), J8.B9 (VBUS), U1.2 (A), U6.5 (VBUS)
+3.3V: C5.2, C6.1, C7.1, C10.1, C11.1, C12.1, J1.7, J1.8, J9.3 (VCC), L201.1, R9.2, R20.1, SW2.2, U2.1 (VBAT), U2.23 (VDD), U2.35 (VDD), U2.48 (VDD), U4.5 (VOUT)
+3.3VA: C211.1, C212.1, L201.2, U2.20 (VREF+), U2.21 (VDDA)
+5V: BZ1.1 (+), C4.1, C13.1, C17.1, C19.1, J1.1, J1.2, J3.5, J4.2, J6.1, J_Switch1.2, R15.1, U4.1 (VIN), U4.3 (STBY)
/Alim/Charge_Batterie: C14.1, R2.2, R10.1, U2.17 (PB0)
/Modules/Bt_RXD: J4.5, U2.10 (PA2)
/Modules/Bt_TXD: J4.4, U2.11 (PA3)
/Modules/Culomn1: J5.5, R1.1, U2.29 (PC6)
/Modules/Culomn2: J5.6, R23.1, U2.30 (PA8)
/Modules/Culomn3: J5.7, R17.1, U2.31 (PA9)
/Modules/Culomn4: J5.8, R19.1, U2.32 (PA10)
/Modules/I2C1_SCL: J6.4, U2.45 (PB7)
/Modules/I2C1_SDA: J6.3, U2.38 (PA15)
/Modules/IRQ: J3.8, U2.39 (PC10)
/Modules/KEY: J4.6, U2.8 (PA0)
/Modules/R0W1: J5.1, U2.25 (PB12)
/Modules/ROW2: J5.2, U2.26 (PB13)
/Modules/ROW3: J5.3, U2.27 (PB14)
/Modules/ROW4: J5.4, U2.28 (PB15)
/Modules/RSTO: J3.2, U2.47 (PB9)
/Modules/SPI1_Miso: J3.7, U2.42 (PB4)
/Modules/SPI1_Mosi: J3.4, U2.43 (PB5)
/Modules/SPI1_SCK: J3.1, U2.13 (PA5)
/Modules/SS: J3.3, U2.44 (PB6)
/Modules/STATE: J4.1, U2.14 (PA6)
/STM32/BL_LED: R13.1, U2.12 (PA4)
/STM32/BOOT0: R6.1, SW2.1, U2.46 (PB8)
/STM32/BUZZER: R8.1, U2.19 (PB2)
/STM32/Bt_Button: C16.1, R7.2, R9.1, U2.9 (PA1)
/STM32/D+: J8.A6 (D+), J8.B6 (D+), U6.6 (I/O1)
/STM32/D-: J8.A7 (D-), J8.B7 (D-), U6.4 (I/O2)
/STM32/NRST: C18.2, J9.12 (~RST), SW3.2, U2.7 (PG10)
/STM32/PA7: J1.11, U2.15 (PA7)
/STM32/PC4: J1.5, U2.16 (PC4)
/STM32/PC13: J1.3, U2.2 (PC13)
/STM32/PC14: J1.4, U2.3 (PC14)
/STM32/PC15: J1.6, U2.4 (PC15)
/STM32/PF0: J1.10, U2.5 (PF0)
/STM32/PF1: J1.9, U2.6 (PF1)
/STM32/Pb1: J1.12, U2.18 (PB1)
/STM32/RFID_LED: R14.1, U2.40 (PC11)
/STM32/SWCLK: J9.6 (JCLK/SWCLK), U2.37 (PA14)
/STM32/SWDIO: J9.4 (JTMS/SWDIO), U2.36 (PA13)
/STM32/SWO: J9.8 (JTDO/SWO), U2.41 (PB3)
/STM32/USART3_RX: J9.14 (VCP_TX), U2.22 (PB10)
/STM32/USART3_TX: J9.13 (VCP_RX), U2.24 (PB11)
/STM32/USB_D+: U2.34 (PA12), U6.1 (I/O1)
/STM32/USB_D-: U2.33 (PA11), U6.3 (I/O2)
GND: C1.2, C2.2, C3.2, C4.2, C5.1, C6.2, C7.2, C10.2, C11.2, C12.2, C13.2, C14.2, C16.2, C17.2, C18.1, C19.2, C211.2, C212.2, D1.1 (K), D2.1 (K), D3.1 (K), D4.1 (K), D5.1 (K), H1.1, H2.1, H3.1, H4.1, J1.13, J1.14, J3.6, J4.3, J6.2, J7.2, J8.A1 (GND), J8.A12 (GND), J8.B1 (GND), J8.B12 (GND), J8.S1 (SHIELD), J9.5 (GND), J9.7 (GND), J9.11 (GNDDetect), Q2.2 (E), R1.2, R3.2, R5.2, R6.2, R10.2, R11.2, R12.2, R17.2, R19.2, R23.2, SW1.1, SW3.1, U2.49 (VSS), U3.10 (AGND), U3.13 (PGND), U4.2 (GND), U6.2 (GND)
unnamed: BZ1.2 (-), Q2.3 (C)
unnamed: D1.2 (A), R13.2
unnamed: D2.2 (A), R14.2
unnamed: D3.2 (A), R15.2
unnamed: D4.2 (A), R21.2
unnamed: D5.2 (A), R20.2
unnamed: J8.A5 (CC1), R11.1
unnamed: J8.B5 (CC2), R12.1
unnamed: J_Switch1.1, U1.1 (K)
unnamed: J_Switch1.3, U5.1 (K)
unnamed: Q2.1 (B), R8.2
unnamed: R7.1, SW1.2
unnamed: U3.9 (VIN), U3.12 (EN)
unnamed: R4.2, R5.1, U3.2 (FB)
unnamed: R3.1, U3.1 (FSW_1)
unnamed: C2.1, U3.3 (Vcc)
VCC: C1.1, J7.1, R2.1, R21.1, U3.4 (Vin), U3.5 (Vin)

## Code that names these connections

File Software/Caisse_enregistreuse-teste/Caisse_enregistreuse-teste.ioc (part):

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Mcu.Name=STM32L476R(C-E-G)Tx
Mcu.Package=LQFP64
Mcu.UserName=STM32L476RGTx
PA0.Signal=S_TIM2_CH1
PA13\ (JTMS-SWDIO).GPIOParameters=GPIO_Label
PA13\ (JTMS-SWDIO).GPIO_Label=TMS
PA13\ (JTMS-SWDIO).Mode=Serial_Wire
PA13\ (JTMS-SWDIO).Signal=SYS_JTMS-SWDIO
PA14\ (JTCK-SWCLK).GPIOParameters=GPIO_Label
PA14\ (JTCK-SWCLK).GPIO_Label=TCK
PA14\ (JTCK-SWCLK).Mode=Serial_Wire
PA14\ (JTCK-SWCLK).Signal=SYS_JTCK-SWCLK
PA15\ (JTDI).GPIOParameters=GPIO_Speed,PinState,GPIO_PuPd,GPIO_Label
PA15\ (JTDI).GPIO_Label=nCS
PA15\ (JTDI).GPIO_PuPd=GPIO_NOPULL
PA15\ (JTDI).GPIO_Speed=GPIO_SPEED_FREQ_HIGH
PA15\ (JTDI).PinState=GPIO_PIN_SET
PA15\ (JTDI).Signal=GPIO_Output
PA2.GPIOParameters=GPIO_Speed,GPIO_PuPd,GPIO_Label,GPIO_Mode
PA2.GPIO_Label=USART_TX
PA2.GPIO_Mode=GPIO_MODE_AF_PP
PA2.GPIO_PuPd=GPIO_NOPULL
PA2.GPIO_Speed=GPIO_SPEED_FREQ_VERY_HIGH
PA2.Mode=Asynchronous
PA2.Signal=USART2_TX
PA3.GPIOParameters=GPIO_Speed,GPIO_PuPd,GPIO_Label,GPIO_Mode
PA3.GPIO_Label=USART_RX
PA3.GPIO_Mode=GPIO_MODE_AF_PP
PA3.GPIO_PuPd=GPIO_NOPULL
PA3.GPIO_Speed=GPIO_SPEED_FREQ_VERY_HIGH
PA3.Mode=Asynchronous
PA3.Signal=USART2_RX
PA5.GPIOParameters=GPIO_Speed,GPIO_PuPd,GPIO_Label,GPIO_ModeDefaultOutputPP
PA5.GPIO_Label=green
PA5.GPIO_ModeDefaultOutputPP=GPIO_MODE_OUTPUT_PP
PA5.GPIO_PuPd=GPIO_NOPULL
PA5.GPIO_Speed=GPIO_SPEED_FREQ_LOW
PA5.Signal=GPIO_Output
PA8.Signal=GPIO_Output
PA9.Signal=GPIO_Output
PB10.Mode=Full_Duplex_Master
PB10.Signal=SPI2_SCK
PB14.GPIOParameters=GPIO_PuPd,GPIO_ModeDefaultEXTI
PB14.GPIO_ModeDefaultEXTI=GPIO_MODE_IT_FALLING
PB14.GPIO_PuPd=GPIO_PULLUP
PB14.Signal=GPXTI14
PB15.GPIOParameters=GPIO_PuPd,GPIO_ModeDefaultEXTI
PB15.GPIO_ModeDefaultEXTI=GPIO_MODE_IT_FALLING
PB15.GPIO_PuPd=GPIO_PULLUP
PB15.Signal=GPXTI15
PB7.GPIOParameters=GPIO_Speed
PB7.GPIO_Speed=GPIO_SPEED_FREQ_HIGH
PB7.Signal=GPIO_Output
PC10.GPIOParameters=GPIO_PuPd
PC10.GPIO_PuPd=GPIO_PULLUP
PC10.Signal=GPIO_Input
PC13.GPIOParameters=GPIO_PuPd,GPIO_Label,GPIO_ModeDefaultEXTI
PC13.GPIO_Label=B1 [Blue PushButton]
PC13.GPIO_ModeDefaultEXTI=GPIO_MODE_IT_FALLING
PC13.GPIO_PuPd=GPIO_PULLUP
PC13.Signal=GPXTI13
PC14-OSC32_IN\ (PC14).Mode=LSE-External-Oscillator
PC14-OSC32_IN\ (PC14).Signal=RCC_OSC32_IN
PC15-OSC32_OUT\ (PC15).Mode=LSE-External-Oscillator
PC15-OSC32_OUT\ (PC15).Signal=RCC_OSC32_OUT
PC2.Mode=Full_Duplex_Master
PC2.Signal=SPI2_MISO
PC3.Mode=Full_Duplex_Master
PC3.Signal=SPI2_MOSI
PC6.GPIOParameters=GPIO_PuPd,GPIO_ModeDefaultEXTI
PC6.GPIO_ModeDefaultEXTI=GPIO_MODE_IT_FALLING
PC6.GPIO_PuPd=GPIO_PULLUP
PC6.Signal=GPXTI6
PC7.GPIOParameters=GPIO_PuPd,GPIO_ModeDefaultEXTI
PC7.GPIO_ModeDefaultEXTI=GPIO_MODE_IT_FALLING
PC7.GPIO_PuPd=GPIO_PULLUP
PC7.Signal=GPXTI7
PC8.Signal=GPIO_Output
PC9.Signal=GPIO_Output
PH0-OSC_IN\ (PH0).Mode=HSE-External-Oscillator
PH0-OSC_IN\ (PH0).Signal=RCC_OSC_IN
PH1-OSC_OUT\ (PH1).Mode=HSE-External-Oscillator
PH1-OSC_OUT\ (PH1).Signal=RCC_OSC_OUT
RCC.HSE_VALUE=8000000
RCC.SYSCLKFreq_VALUE=80000000
RCC.SYSCLKSource=RCC_SYSCLKSOURCE_PLLCLK
board=NUCLEO-L476RG
boardIOC=true
